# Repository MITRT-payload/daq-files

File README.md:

# daq-files
For the data acquisition

DAQ Files for Hermes III under daqr2/

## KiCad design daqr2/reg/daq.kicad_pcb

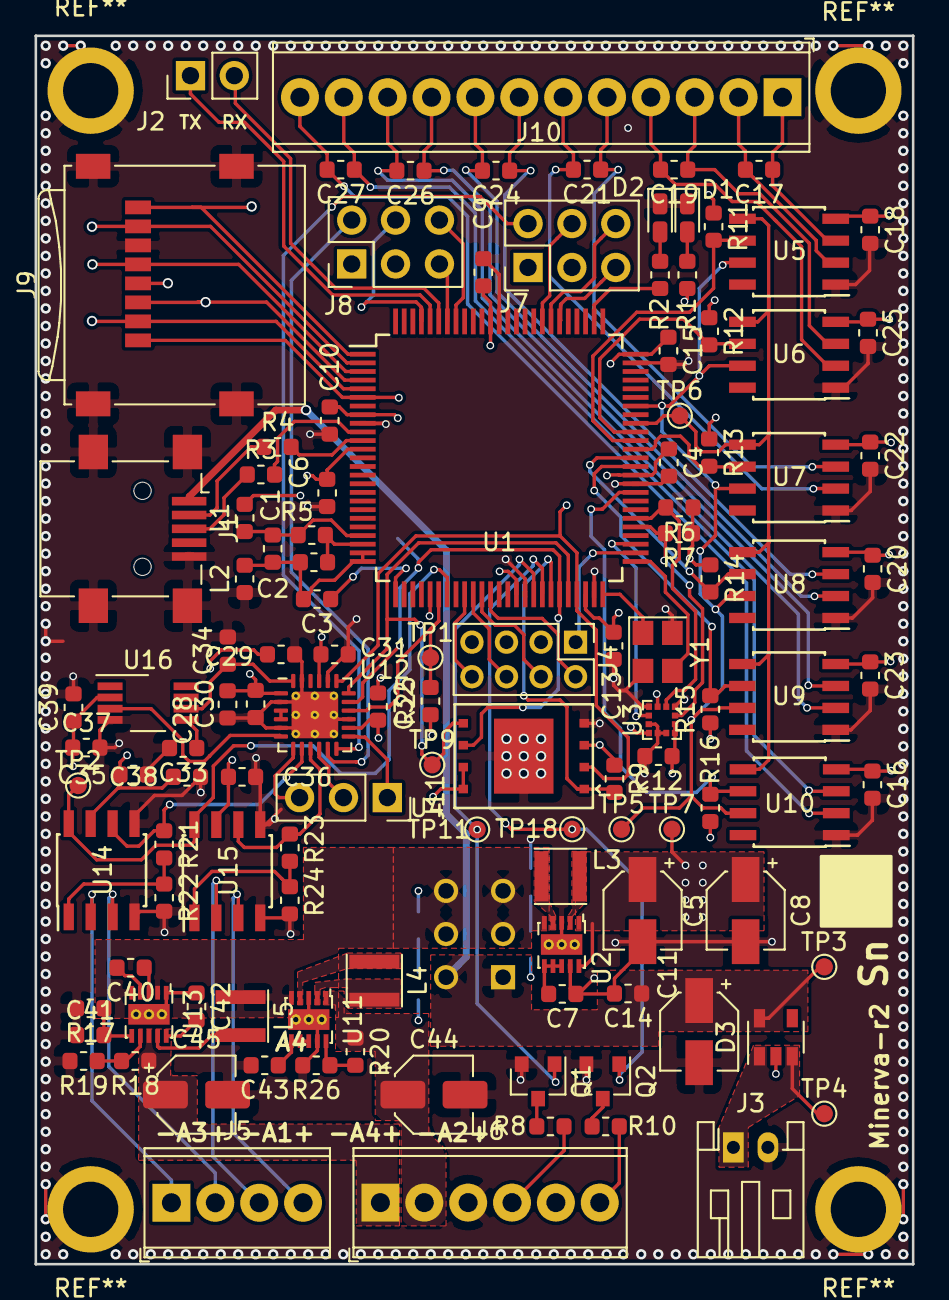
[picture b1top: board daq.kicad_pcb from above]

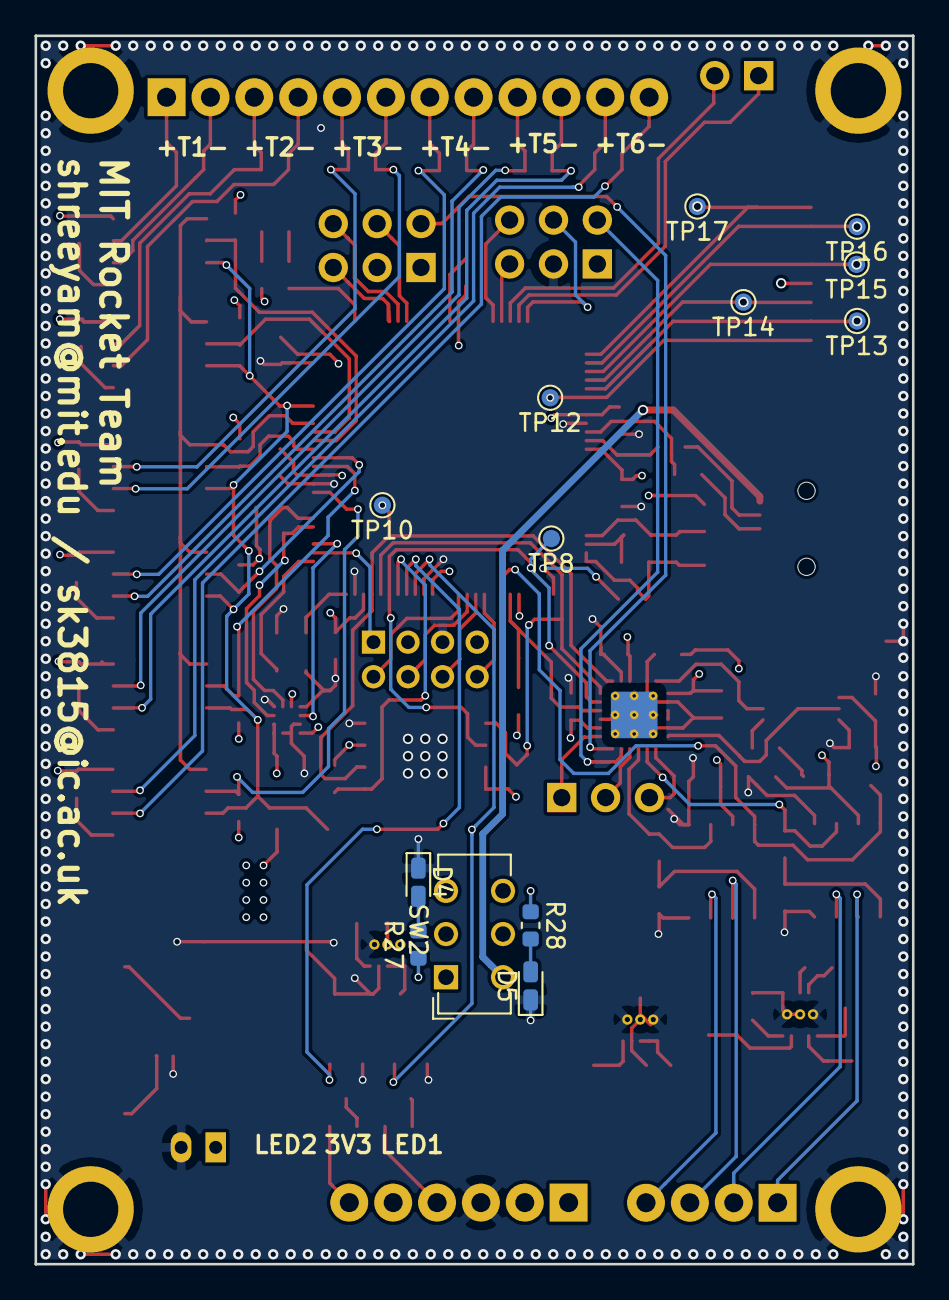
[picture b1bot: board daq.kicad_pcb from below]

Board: 4 copper layers, 50.8 x 71.1 mm, 132 parts (13 on the bottom side), 106 nets.

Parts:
C1, C29, C30, C31, C32: 2.2uF; C_0603_1608Metric
C2, C3, C4, C6, C7, C9, C10, C12, C13, C14, C15, C16, C18, C20, C22, C23, C25, C28, C35, C36, C38, C39, C43: 100nF; C_0603_1608Metric
C5, C8, C11, C44, C45: 10uF; CP_Elec_4x5.8
C17, C19, C21, C24, C26, C27: 10nF; C_0603_1608Metric
C33, C37: 1uF; C_0603_1608Metric
C34: 10uF; C_0603_1608Metric
C40, C42: 100n; C_0603_1608Metric
C41: 1u; C_0603_1608Metric
D1, D2, D4, D5: LED; LED_0603_1608Metric_Castellated
D3: MAX40200; SOT-23-5
J1: USB_B_Mini; USB_Mini-B_Lumberg_2486_01_Horizontal
J2: Conn_01x02; PinHeader_1x02_P2.54mm_Vertical
J3: Battery; JST_PH_S2B-PH-K_1x02_P2.00mm_Horizontal
J4: Programmer; PinHeader_2x04_P2.00mm_Vertical
J5: Screw_Terminal_01x04; TerminalBlock_Phoenix_MPT-0,5-4-2.54_1x04_P2.54mm_Horizontal
J6: Driven LEDs; TerminalBlock_Phoenix_MPT-0,5-6-2.54_1x06_P2.54mm_Horizontal
J7: Accelerometer 1; PinHeader_2x03_P2.54mm_Vertical
J8: Accelerometer 2; PinHeader_2x03_P2.54mm_Vertical
J9: Micro_SD_Card; microSD_HC_Wuerth_693072010801
J10: Thermocouple Input; TerminalBlock_Phoenix_MPT-0,5-12-2.54_1x12_P2.54mm_Horizont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
J11: Conn_01x02; PinSocket_1x03_P2.54mm_Vertical
L1, L2: L_Core_Ferrite; L_0603_1608Metric
L3, L4: 1.5uH; L_Taiyo-Yuden_NR-30xx
L5: 10u; L_Taiyo-Yuden_NR-30xx
Q1, Q2: Q_NMOS_GSD; SOT-23
R1, R2, R5, R27, R28: 470; R_0603_1608Metric
R3, R4, R8, R10: 33; R_0603_1608Metric
R6, R7: 4k7; R_0603_1608Metric
R9, R11, R12, R13, R14, R15, R16, R19, R25: 10k; R_0603_1608Metric
R17: 200k; R_0603_1608Metric
R18: 230k; R_0603_1608Metric
R20: 180k; R_0603_1608Metric
R21: 30k; R_0603_1608Metric
R22, R24: 1k; R_0603_1608Metric
R23: 100k; R_0603_1608Metric
R26: 20k; R_0603_1608Metric
SW2: SW_DPDT_x2; SW_CuK_JS202011CQN_DPDT_Straight
TP1: CSANLG; TestPoint_Pad_D1.0mm
TP2: CAL; TestPoint_Pad_D1.0mm
TP3: VDD; TestPoint_Pad_D1.0mm
TP4: +BATT; TestPoint_Pad_D1.0mm
TP5, TP6: TestPoint; TestPoint_Pad_D1.0mm
TP7: +3V3; TestPoint_Pad_D1.0mm
TP8: SPI0_SCLK; TestPoint_Pad_D1.0mm
TP9: SPI0_MOSI; TestPoint_Pad_D1.0mm
TP10: SPI0_MISO; TestPoint_Pad_D1.0mm
TP11: LEDE1; TestPoint_Pad_D1.0mm
TP12: SD_DAT2; TestPoint_Pad_D1.0mm
TP13: SD_DAT3; TestPoint_Pad_D1.0mm
TP14: SD_CMD; TestPoint_Pad_D1.0mm
TP15: SD_CLK; TestPoint_Pad_D1.0mm
TP16: SD_DAT0; TestPoint_Pad_D1.0mm
TP17: SD_DAT1; TestPoint_Pad_D1.0mm
TP18: LEDE2; TestPoint_Pad_D1.0mm
U1: MK64F; LQFP-100_14x14mm_P0.5mm
U2: TPS63031; VSON-10-1EP_2.5x2.5mm_Pitch0.5mm_ThermalPad
U3: KXTJ3-1057; LGA-12_2x2mm_P0.5mm
U4: W25N01GV; WSON-8 8x6mm
U5, U6, U7, U8, U9, U10: MAX31855KASA; SOIC-8_3.9x4.9mm_P1.27mm
U11: TPS63030; VSON-10-1EP_2.5x2.5mm_Pitch0.5mm_ThermalPad
U12: ADS7951; QFN-24-1EP_4x4mm_P0.5mm_EP2.7x2.7mm_ThermalVias
U13: TPS61093; VSON-10-1EP_2.5x2.5mm_Pitch0.5mm_ThermalPad
U14, U15: MCP6N11; SOIC-8_3.9x4.9mm_P1.27mm
U16: REF5025ADGK; VSSOP-8_3.0x3.0mm_P0.65mm
Y1: 16 MHz; Crystal_SMD_3225-4Pin_3.2x2.5mm

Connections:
+3V3: C4.1, C5.1, C6.1, C8.1, C9.1, C10.1, C12.1, C13.1, C15.1, C16.1, C18.1, C20.1, C22.1, C23.1, C25.1, C28.1, C29.1, C30.1, C31.1, C32.1, C35.1, C36.1, C37.1, C38.1, C39.1, J4.3, J6.5, J7.1, J8.1, J9.4, L1.2, R1.1, R6.1, R7.1, R9.1, R11.1, R12.1, R13.1, R14.1, R15.1, R16.1, R25.1, R27.1, R28.1, TP7.1, U1.8, U1.12, U1.30, U1.40, U1.48, U1.61, U1.75, U1.89, U2.1, U2.10, U3.3, U3.7, U3.10, U3.11, U4.3, U4.7, U4.8, U5.4, U6.4, U7.4, U8.4, U9.4, U10.4, U12.1, U12.14, U12.21, U14.7, U15.7, U16.2
+5V: C44.1, J6.2, R20.1, U11.1
+10V: C45.1, J6.1, R18.1, U13.8
+BATT: D3.1, D3.3, J3.1, TP4.1
/ACC_INT: U1.53, U3.5
/CAL_ANLG: TP2.1, U1.32, U14.8, U15.8
/CS_ANLG: R25.2, TP1.1, U1.31, U12.16
/CS_FLASH: R9.2, U1.44, U4.1
/CS_TC1: R11.2, U1.65, U5.6
/CS_TC2: R12.2, U1.66, U6.6
/CS_TC3: R13.2, U1.64, U7.6
/CS_TC4: R14.2, U1.63, U8.6
/CS_TC5: R15.2, U1.62, U9.6
/CS_TC6: R16.2, U1.59, U10.6
/D+: R3.2, U1.10
/D-: R4.2, U1.11
/IM3: J5.1, U14.2
/IM4: J5.3, U15.2
/IP3: J5.2, U14.3
/IP4: J5.4, U15.3
/JTAG_TCLK: J4.8, U1.34
/JTAG_TDI: J4.6, U1.35
/JTAG_TDO: J4.4, U1.36
/JTAG_TMS: J4.2, U1.37
/LED: R2.1, U1.77
/LED_E1: Q1.1, TP11.1, U1.42
/LED_E2: Q2.1, TP18.1, U1.43
/OR_1: J7.4, U1.83
/OR_2: J8.4, U1.97
/OSC_1: U1.50, Y1.1
/OSC_2: U1.51, Y1.3
/RST: J4.1, U1.52
/SCL: R7.2, U1.55, U3.12
/SDA: R6.2, U1.56, U3.2
/SD_CLK: J9.5, TP15.1, U1.3
/SD_CMD: J9.3, TP14.1, U1.4
/SD_DAT0: J9.7, TP16.1, U1.2
/SD_DAT1: J9.8, TP17.1, U1.1
/SD_DAT2: J9.1, TP12.1, U1.6
/SD_DAT3: J9.2, TP13.1, U1.5
/SPI0_MISO: TP10.1, U1.47, U4.2, U12.19
/SPI0_MOSI: TP9.1, U1.46, U4.5, U12.18
/SPI0_SCLK: TP8.1, U1.45, U4.6, U12.17
/SPI2_MISO: TP5.1, U1.69, U5.7, U6.7, U7.7, U8.7, U9.7, U10.7
/SPI2_SCLK: TP6.1, U1.67, U5.5, U6.5, U7.5, U8.5, U9.5, U10.5
/STBY_1: J7.6, U1.82
/STBY_2: J8.6, U1.93
/ST_1: J7.5, U1.81
/ST_2: J8.5, U1.94
/UART_RX: J2.2, U1.95
/UART_TX: J2.1, U1.96
/V_ACC_1: J7.2, U12.12
/V_ACC_2: J8.2, U12.11
/analog/CHIP_TEMP: U12.6, U16.3
/analog/FG3: R21.2, R22.1, U14.1
/analog/FG4: R23.2, R24.1, U15.1
/analog/OUT0: J11.1, U12.13
/analog/OUT1: J11.3, U12.7
/analog/OUT2: J11.2, U12.10
/analog/OUT3: R21.1, U12.8, U14.6
/analog/OUT4: R23.1, U12.9, U15.6
/analog/REFP: C34.1, U12.24, U16.6
/thermocouples/T1+: C17.1, J10.1, U5.3
/thermocouples/T1-: C17.2, J10.2, U5.2
/thermocouples/T2+: C19.1, J10.3, U6.3
/thermocouples/T2-: C19.2, J10.4, U6.2
/thermocouples/T3+: C21.1, J10.5, U7.3
/thermocouples/T3-: C21.2, J10.6, U7.2
/thermocouples/T4+: C24.1, J10.7, U8.3
/thermocouples/T4-: C24.2, J10.8, U8.2
/thermocouples/T5+: C26.1, J10.9, U9.3
/thermocouples/T5-: C26.2, J10.10, U9.2
/thermocouples/T6+: C27.1, J10.11, U10.3
/thermocouples/T6-: C27.2, J10.12, U10.2
GND: C4.2, C5.2, C6.2, C7.2, C8.2, C9.2, C10.2, C11.2, C12.2, C13.2, C14.2, C15.2, C16.2, C18.2, C20.2, C22.2, C23.2, C25.2, C28.2, C29.2, C30.2, C31.2, C32.2, C33.2, C34.2, C35.2, C36.2, C37.2, C38.2, C39.2, C41.1, C42.1, C43.2, C44.2, C45.2, D1.1, D2.1, D3.2, D4.1, D5.1, J1.5, J1.6, J3.2, J4.5, J4.7, J6.3, J7.3, J8.3, J9.6, J9.9, L2.1, Q1.2, Q2.2, R17.2, R19.2, R22.2, R24.2, R26.2, U1.9, U1.41, U1.49, U1.60, U1.74, U1.88, U2.3, U2.9, U2.11, U3.1, U3.4, U3.6, U3.8, U3.9, U4.4, U4.9, U5.1, U6.1, U7.1, U8.1, U9.1, U10.1, U11.3, U11.9, U11.11, U12.2, U12.5, U12.15, U12.20, U12.23, U12.25, U13.1, U13.11, U14.4, U14.5, U15.4, U15.5, U16.4, Y1.2, Y1.4
unnamed: C1.1, C2.2, C3.2, L2.2, U1.24, U1.25
unnamed: C1.2, L1.1, R5.2, U1.22
unnamed: C2.1, R5.1, U1.23
unnamed: C3.1, U1.26
unnamed: C7.1, U2.6, U2.7, U2.8
unnamed: C33.1, U16.5
unnamed: C40.1, U13.3
unnamed: C40.2, U13.4
unnamed: C41.2, R17.1, U13.6
unnamed: C42.2, U13.10
unnamed: C43.1, U11.6, U11.7, U11.8
unnamed: D1.2, R1.2
unnamed: D2.2, R2.2
unnamed: D4.2, R27.2
unnamed: D5.2, R28.2
unnamed: J1.2, R4.1
unnamed: J1.3, R3.1
unnamed: J6.4, R8.1
unnamed: J6.6, R10.1
unnamed: L3.1, U2.4
unnamed: L3.2, U2.2
unnamed: L4.1, U11.4
unnamed: L4.2, U11.2
unnamed: L5.1, SW2.2, SW2.3, SW2.5, SW2.6, U2.5, U11.5, U13.2, U13.5
unnamed: L5.2, U13.9
unnamed: Q1.3, R8.2
unnamed: Q2.3, R10.2
unnamed: R18.2, R19.1, U13.7
unnamed: R20.2, R26.1, U11.10
unnamed: U12.3, U12.4
VDD: C11.1, C14.1, D3.5, J1.1, SW2.1, SW2.4, TP3.1

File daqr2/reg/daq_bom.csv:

Ref,Qnty,Value,Cmp name,Footprint,Description,Digikey Part Number,URL,Unit Cost,Total Cost
"C1, C29, C30, C31, C32, ",5,2.2uF,C,Capacitor_SMD:C_0603_1608Metric,Unpolarized capacitor,1276-1085-1-ND,https://www.digikey.com/product-detail/en/samsung-electro-me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,0.12,0.60
"C5, C8, C11, ",3,10uF,C,Capacitor_SMD:CP_Elec_4x5.8,Unpolarized capacitor,PCE3878CT-ND,https://www.digikey.com/product-detail/en/panasonic-electron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,0.30,0.90
"C7, C2, C3, C4, C6, C9, C10, C13, C15, C14, C12, C22, C23, C25, C16, C18, C20, C35, C36, C38, C40, C41, C28, C39, ",24,100nF,C,Capacitor_SMD:C_0603_1608Metric,Unpolarized capacitor,1276-1000-1-ND,https://www.digikey.com/product-detail/en/samsung-electro-me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,0.04,0.84
"C17, C19, C21, C24, C26, C27, ",12,10nF,C,Capacitor_SMD:C_0603_1608Metric,Unpolarized capacitor,1276-1921-1-ND,https://www.digikey.com/product-detail/en/samsung-electro-me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,0.03,0.40
"C33, C37, ",10,1uF,C,Capacitor_SMD:C_0603_1608Metric,Unpolarized capacitor,1276-1036-1-ND,https://www.digikey.com/product-detail/en/samsung-electro-me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,0.03,0.31
"C34, ",1,10uF,C,Capacitor_SMD:C_0603_1608Metric,Unpolarized capacitor,587-5869-1-ND,https://www.digikey.com/product-detail/en/taiyo-yuden/JMK107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,0.15,0.15
"D1, D2, ",2,LED,LED,LED_SMD:LED_0603_1608Metric_Castellated,LED generic,732-4971-1-ND,https://www.digikey.com/product-detail/en/wurth-electronics-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,0.15,0.30
"D3, ",1,MAX40200,MAX40200,Package_TO_SOT_SMD:SOT-23-5,,MAX40200AUK+TCT-ND,https://www.digikey.com/product-detail/en/maxim-integrated/M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,0.93,0.93
"J1, ",1,USB_B_Mini,USB_B_Micro,Connector_USB:USB_Mini-B_Lumberg_2486_01_Horizontal,USB Micro Type B connector,151-1206-1-ND,https://www.digikey.com/product-detail/en/edac-inc/690-005-2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,0.60,0.60
"J3, ",1,Battery,Conn_01x02,Connector_JST:JST_PH_S2B-PH-K_1x02_P2.00mm_Horizontal,"Generic connector, single row, 01x02, script generated (kicad-library-utils/schlib/autogen/connector/)",WM14854-ND,https://www.digikey.com/products/en?keywords=894010210,0.14,0.14
"J4, ",1,Programmer,Conn_02x04_Odd_Even,Connector_PinHeader_2.00mm:PinHeader_2x04_P2.00mm_Vertical,"Generic connector, double row, 02x04, odd/even pin numbering scheme (row 1 odd numbers, row 2 even numbers), script generated (kicad-library-utils/schlib/autogen/connector/)",A108094-ND,https://www.digikey.com/products/en?keywords=2-1734506-7,0.59,0.59
"J5, ",1,Pressure Tap/Load Cell,Screw_Terminal_01x08,"TerminalBlock_Phoenix:TerminalBlock_Phoenix_MPT-0,5-8-2.54_1x08_P2.54mm_Horizontal","Generic screw terminal, single row, 01x08, script generated (kicad-library-utils/schlib/autogen/connector/)",ED10566-ND,https://www.digikey.com/product-detail/en/on-shore-technolog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,2.36,2.36
"J6, ",1,Driven LEDs,Screw_Terminal_01x03,"custom:TerminalBlock_Phoenix_MPT-0,5-3-2.54_1x03_P2.54mm_Horizontal","Generic screw terminal, single row, 01x03, script generated (kicad-library-utils/schlib/autogen/connector/)",ED10562-ND,https://www.digikey.com/product-detail/en/on-shore-technolog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,1.03,1.03
"J7, J8",2,Accelerometer,Conn_02x03_Odd_Even,Connector_PinHeader_2.54mm:PinHeader_2x03_P2.54mm_Vertical,"Generic connector, double row, 02x03, odd/even pin numbering scheme (row 1 odd numbers, row 2 even numbers), script generated (kicad-library-utils/schlib/autogen/connector/)",S7071-ND,https://www.digikey.com/product-detail/en/sullins-connector-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,0.61,1.22
"J9, ",1,Micro_SD_Card,Micro_SD_Card,Connector_Card:microSD_HC_Wuerth_693072010801,Micro SD Card Socket,732-3820-1-ND,https://www.digikey.com/product-detail/en/wurth-electronics-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,3.42,3.42
"J10, ",1,Thermocouple Input,Screw_Terminal_01x12,"TerminalBlock_Phoenix:TerminalBlock_Phoenix_MPT-0,5-12-2.54_1x12_P2.54mm_Horizontal","Generic screw terminal, single row, 01x12, script generated (kicad-library-utils/schlib/autogen/connector/)",ED10568-ND,https://www.digikey.com/product-detail/en/on-shore-technolog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,3.16,3.16
"L1, L2, ",2,L_Core_Ferrite,L_Core_Ferrite,Inductor_SMD:L_0603_1608Metric,Inductor with Ferrite Core,1276-6351-1-ND,https://www.digikey.com/product-detail/en/samsung-electro-me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,0.10,0.20
"L3, ",1,1.5uH,L,Inductor_SMD:L_Taiyo-Yuden_NR-30xx,Inductor,587-2617-1-ND,https://www.digikey.com/product-detail/en/taiyo-yuden/NR3015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,0.41,0.41
"Q1, Q2, ",2,Q_NMOS_GSD,Q_NMOS_GSD,Package_TO_SOT_SMD:SOT-23,Transistor N-MOSFETwith substrate diode (general),NTR5103NT1GOSCT-ND,https://www.digikey.com/product-detail/en/on-semiconductor/N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,0.18,0.36
"R5, R1, R2, ",3,470,R,Resistor_SMD:R_0603_1608Metric,Resistor,311-470GRCT-ND,https://www.digikey.com/product-detail/en/yageo/RC0603JR-074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,0.10,0.30
"R6, R7, ",10,4k7,R,Resistor_SMD:R_0603_1608Metric,Resistor,311-4.7KGRCT-ND,https://www.digikey.com/product-detail/en/yageo/RC0603JR-074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,0.02,0.20
"R8, R10, R4, R3, ",4,33,R,Resistor_SMD:R_0603_1608Metric,Resistor,311-33.0HRCT-ND,https://www.digikey.com/product-detail/en/yageo/RC0603FR-073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,0.10,0.40
"R9, R11, R12, R13, R14, R15, R16, R25, ",20,10k,R,Resistor_SMD:R_0603_1608Metric,Resistor,RMCF0603JT10K0CT-ND,https://www.digikey.com/product-detail/en/stackpole-electron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,0.02,0.32
"R17, R19, R21, ",10,30k,R,Resistor_SMD:R_0603_1608Metric,Resistor,RMCF0603JT30K0CT-ND,https://www.digikey.com/product-detail/en/stackpole-electron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,0.02,0.16
"R18, R20, R22, R24, ",10,1k,R,Resistor_SMD:R_0603_1608Metric,Resistor,RMCF0603FT1K00CT-ND,https://www.digikey.com/product-detail/en/stackpole-electron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,0.02,0.18
"R23, ",10,100k,R,Resistor_SMD:R_0603_1608Metric,Resistor,CR0603-JW-104ELFCT-ND,https://www.digikey.com/product-detail/en/bourns-inc/CR0603-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,0.02,0.15
"SW1, ",1,SW_SPST,SW_SPST,Button_Switch_THT:SW_DIP_SPSTx01_Slide_9.78x4.72mm_W7.62mm_P2.54mm,Single Pole Single Throw (SPST) switch,Z5195-ND,https://www.digikey.com/product-detail/en/omron-electronics-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,0.90,0.90
"U1, ",1,MK64F,MK64F,Package_QFP:LQFP-100_14x14mm_P0.5mm,,MK64FX512VLL12-ND,https://www.digikey.com/product-detail/en/nxp-usa-inc/MK64FX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,12.56,12.56
"U2, ",1,TPS63031,TPS63031,custom:VSON-10-1EP_2.5x2.5mm_Pitch0.5mm_ThermalPad,,296-39461-1-ND,https://www.digikey.com/product-detail/en/texas-instruments/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,1.93,1.93
"U3, ",1,KXTJ3-1057,KXTJ3-1057,Package_LGA:LGA-12_2x2mm_P0.5mm,,KXTJ3-1057CT-ND,https://www.digikey.com/product-detail/en/kionix-inc/KXTJ3-1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,1.69,1.69
"U4, ",1,W25N01GV,W25N01GV,custom:WSON-8 8x6mm,,W25N01GVZEIGCT-ND,https://www.digikey.com/product-detail/en/winbond-electronic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,3.27,3.27
"U5, U6, U7, U8, U9, U10, ",6,MAX31855KASA,MAX31855KASA,Package_SO:SOIC-8_3.9x4.9mm_P1.27mm,"Cold Junction K-type Termocouple Interface, SPI, SO8",MAX31855KASA+TCT-ND,https://www.digikey.com/product-detail/en/maxim-integrated/M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,6.52,39.12
"U11, U13, U14, U15, ",4,MCP6N11,MCP6N11,Package_SO:SOIC-8_3.9x4.9mm_P1.27mm,,MCP6N11-010E/SN-ND,https://www.digikey.com/products/en?keywords=MCP6N11-010,1.39,5.56
"U12, ",1,ADS7951,ADS7951,Package_DFN_QFN:QFN-24-1EP_4x4mm_P0.5mm_EP2.7x2.7mm_ThermalVias,,296-25840-1-ND,https://www.digikey.com/product-detail/en/texas-instruments/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,7.44,7.44
"U16, ",1,REF5025ADGK,REF5025ADGK,Package_SO:VSSOP-8_3.0x3.0mm_P0.65mm,"2.5V 0.1% 10mA Low Noise Precision Voltage Reference, MSOP-8",296-41382-1-ND,https://www.digikey.com/product-detail/en/texas-instruments/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,3.00,3.00
"Y1, ",1,16 MHz,Crystal_GND24,Crystal:Crystal_SMD_3225-4Pin_3.2x2.5mm,"Four pin crystal (GND on pins 2 and 4), e.g. in SMD package",644-1099-1-ND,https://www.digikey.com/product-detail/en/ndk-america-inc/NX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,0.92,0.92
,,,,,,,,,96.016

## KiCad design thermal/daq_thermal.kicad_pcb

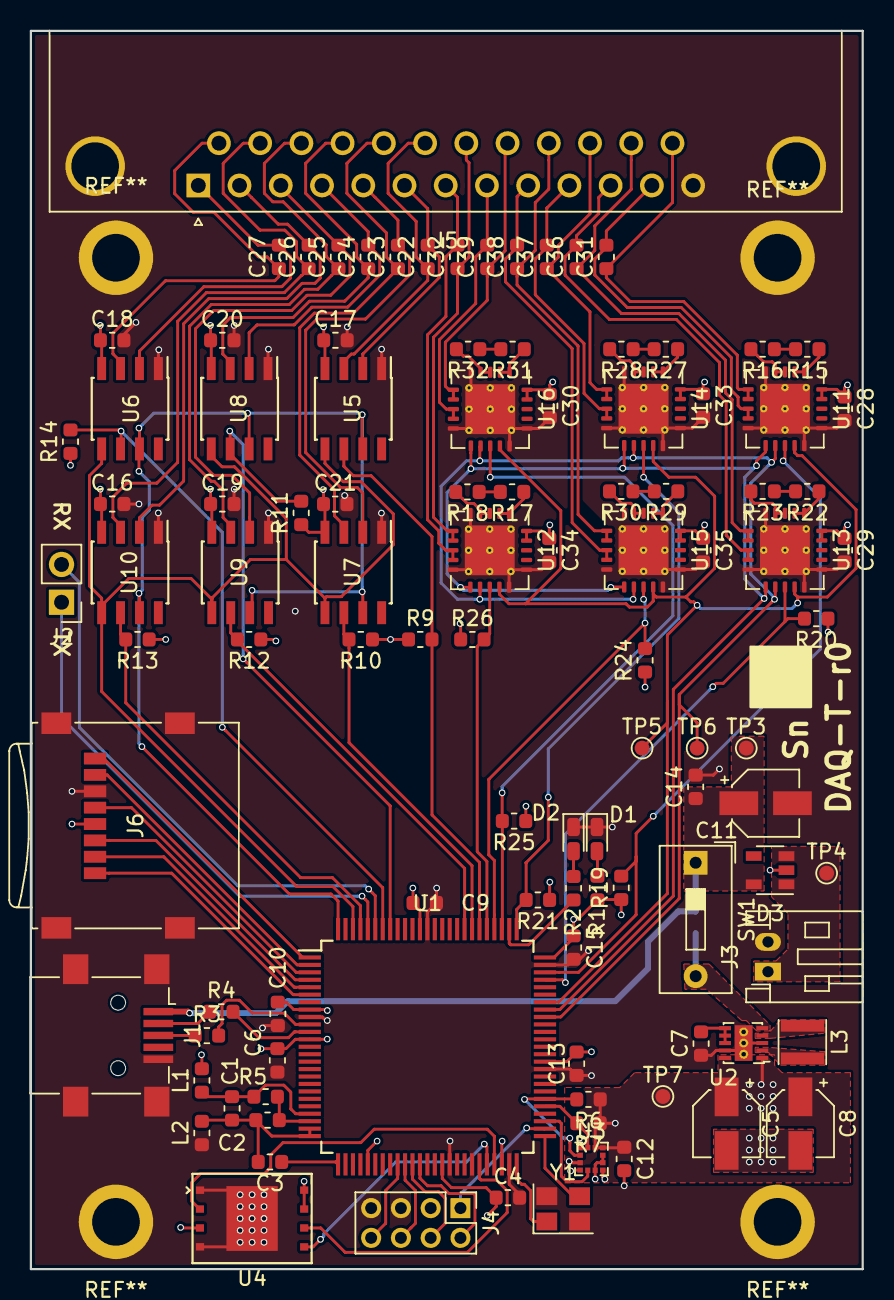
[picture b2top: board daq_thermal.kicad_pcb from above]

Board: 4 copper layers, 55.9 x 83.2 mm, 106 parts (1 on the bottom side), 99 nets.

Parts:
C1: 2.2uF; C_0603_1608Metric
C2, C3, C4, C6, C7, C9, C10, C12, C13, C14, C15, C16, C17, C18, C19, C20, C21: 100nF; C_0603_1608Metric
C5, C8, C11: 10uF; CP_Elec_4x5.8
C22, C23, C24, C25, C26, C27: 10nf; C_0603_1608Metric
C28, C29, C30, C33, C34, C35: 220nF; C_0603_1608Metric
C31, C32, C36, C37, C38, C39: 10nF; C_0603_1608Metric
D1, D2: LED; LED_0603_1608Metric_Castellated
D3: MAX40200; SOT-23-5
J1: USB_B_Mini; USB_Mini-B_Lumberg_2486_01_Horizontal
J2: Conn_01x02; PinHeader_1x02_P2.54mm_Vertical
J3: Battery; JST_PH_S2B-PH-K_1x02_P2.00mm_Horizontal
J4: Programmer; PinHeader_2x04_P2.00mm_Vertical
J5: Dsub25; DSUB-25_Male_Horizontal_P2.77x2.84mm_EdgePinOffset4.94mm_Ho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
J6: Micro_SD_Card; microSD_HC_Wuerth_693072010801
JP1: SolderJumper_2_Open; SolderJumper-2_P1.3mm_Open_TrianglePad1.0x1.5mm
L1, L2: L_Core_Ferrite; L_0603_1608Metric
L3: 1.5uH; L_Taiyo-Yuden_NR-30xx
R1, R2, R5: 470; R_0603_1608Metric
R3, R4: 33; R_0603_1608Metric
R6, R7: 4k7; R_0603_1608Metric
R9, R10, R11, R12, R13, R14, R19, R20, R21, R24, R25, R26: 10k; R_0603_1608Metric
R15, R16, R17, R18, R22, R23, R27, R28, R29, R30, R31, R32: 2k; R_0603_1608Metric
SW1: SW_SPST; SW_DIP_SPSTx01_Slide_9.78x4.72mm_W7.62mm_P2.54mm
TP3: VDD; TestPoint_Pad_D1.0mm
TP4: +BATT; TestPoint_Pad_D1.0mm
TP5, TP6: TestPoint; TestPoint_Pad_D1.0mm
TP7: +3V3; TestPoint_Pad_D1.0mm
U1: MK64F; LQFP-100_14x14mm_P0.5mm
U2: TPS63031; VSON-10-1EP_2.5x2.5mm_Pitch0.5mm_ThermalPad
U3: KXTJ3-1057; LGA-12_2x2mm_P0.5mm
U4: W25N01GV; WSON-8 8x6mm
U5, U6, U7, U8, U9, U10: MAX31855KASA; SOIC-8_3.9x4.9mm_P1.27mm
U11, U12, U13, U14, U15, U16: MAX31865; QFN-20-1EP_5x5mm_P0.65mm_EP3.35x3.35mm_ThermalVias
Y1: 16 MHz; Crystal_SMD_3225-4Pin_3.2x2.5mm

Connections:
+3V3: C4.1, C5.1, C6.1, C8.1, C9.1, C10.1, C12.1, C13.1, C15.1, C16.1, C17.1, C18.1, C19.1, C20.1, C21.1, C28.1, C29.1, C30.1, C33.1, C34.1, C35.1, J4.3, J6.4, L1.2, R1.1, R6.1, R7.1, R9.1, R10.1, R11.1, R12.1, R13.1, R14.1, R19.1, R20.1, R21.1, R24.1, R25.1, R26.1, TP7.1, U1.8, U1.12, U1.30, U1.40, U1.48, U1.61, U1.75, U1.89, U2.1, U2.10, U3.3, U3.7, U3.10, U3.11, U4.3, U4.7, U4.8, U5.4, U6.4, U7.4, U8.4, U9.4, U10.4, U11.19, U11.20, U12.19, U12.20, U13.19, U13.20, U14.19, U14.20, U15.19, U15.20, U16.19, U16.20
+BATT: D3.1, D3.3, J3.1, TP4.1
/ACC_INT: U1.53, U3.5
/CS_RTD1: R19.2, U1.73, U11.13
/CS_RTD2: R20.2, U1.72, U13.13
/CS_RTD3: R21.2, U1.76, U14.13
/CS_RTD4: R24.2, U1.79, U15.13
/CS_RTD5: R25.2, U1.78, U16.13
/CS_RTD6: R26.2, U1.80, U12.13
/CS_TC1: R9.2, U1.81, U5.6
/CS_TC2: R10.2, U1.82, U7.6
/CS_TC3: R11.2, U1.93, U8.6
/CS_TC4: R12.2, U1.83, U9.6
/CS_TC5: R13.2, U1.97, U10.6
/CS_TC6: R14.2, U1.94, U6.6
/D+: R3.2, U1.10
/D-: R4.2, U1.11
/LED: R2.1, U1.77
/OSC_1: U1.50, Y1.1
/OSC_2: U1.51, Y1.3
/PTA0: J4.8, U1.34
/PTA1: J4.6, U1.35
/PTA2: J4.4, U1.36
/PTA3: J4.2, U1.37
/RST: J4.1, U1.52
/RTD1+: C31.1, J5.25, U11.6, U11.7
/RTD1-: C31.2, J5.12, U11.8, U11.9
/RTD2+: C36.1, J5.24, U13.6, U13.7
/RTD2-: C36.2, J5.11, U13.8, U13.9
/RTD3+: C37.1, J5.23, U14.6, U14.7
/RTD3-: C37.2, J5.10, U14.8, U14.9
/RTD4+: C38.1, J5.22, U15.6, U15.7
/RTD4-: C38.2, J5.9, U15.8, U15.9
/RTD5+: C39.1, J5.21, U16.6, U16.7
/RTD5-: C39.2, J5.8, U16.8, U16.9
/RTD6+: C32.1, J5.20, U12.6, U12.7
/RTD6-: C32.2, J5.7, U12.8, U12.9
/SCL: R7.2, U1.55, U3.12
/SDA: R6.2, U1.56, U3.2
/SD_CLK: J6.5, U1.3
/SD_CMD: J6.3, U1.4
/SD_DAT0: J6.7, U1.2
/SD_DAT1: J6.8, U1.1
/SD_DAT2: J6.1, U1.6
/SD_DAT3: J6.2, U1.5
/SPI0_MISO: U1.47, U4.2
/SPI0_MOSI: U1.46, U4.5
/SPI0_SCLK: U1.45, U4.6
/SPI1_MISO: U1.100, U5.7, U6.7, U7.7, U8.7, U9.7, U10.7
/SPI1_SCLK: U1.98, U5.5, U6.5, U7.5, U8.5, U9.5, U10.5
/SPI2_MISO: TP5.1, U1.69, U11.14, U12.14, U13.14, U14.14, U15.14, U16.14
/SPI2_MOSI: U1.68, U11.11, U12.11, U13.11, U14.11, U15.11, U16.11
/SPI2_SCLK: TP6.1, U1.67, U11.12, U12.12, U13.12, U14.12, U15.12, U16.12
/TC1+: C22.1, J5.19, U5.3
/TC1-: C22.2, J5.6, U5.2
/TC2+: C23.1, J5.18, U7.3
/TC2-: C23.2, J5.5, U7.2
/TC3+: C24.1, J5.17, U8.3
/TC3-: C24.2, J5.4, U8.2
/TC4+: C25.1, J5.16, U9.3
/TC4-: C25.2, J5.3, U9.2
/TC5+: C26.1, J5.15, U10.3
/TC5-: C26.2, J5.2, U10.2
/TC6+: C27.1, J5.14, U6.3
/TC6-: C27.2, J5.1, U6.2
/UART_RX: J2.2, U1.95
/UART_TX: J2.1, U1.96
GND: C4.2, C5.2, C6.2, C7.2, C8.2, C9.2, C10.2, C11.2, C12.2, C13.2, C14.2, C15.2, C16.2, C17.2, C18.2, C19.2, C20.2, C21.2, C28.2, C29.2, C30.2, C33.2, C34.2, C35.2, D1.1, D2.1, D3.2, J1.5, J1.6, J3.2, J4.5, J4.7, J5.0, J5.13, J6.6, J6.9, L2.1, U1.9, U1.41, U1.44, U1.49, U1.60, U1.74, U1.88, U2.3, U2.9, U2.11, U3.1, U3.4, U3.6, U3.8, U3.9, U4.1, U4.4, U4.9, U5.1, U6.1, U7.1, U8.1, U9.1, U10.1, U11.5, U11.10, U11.15, U11.16, U11.21, U12.5, U12.10, U12.15, U12.16, U12.21, U13.5, U13.10, U13.15, U13.16, U13.21, U14.5, U14.10, U14.15, U14.16, U14.21, U15.5, U15.10, U15.15, U15.16, U15.21, U16.5, U16.10, U16.15, U16.16, U16.21, Y1.2, Y1.4
unnamed: C1.1, C2.2, C3.2, L2.2, U1.24, U1.25
unnamed: C1.2, L1.1, R5.2, U1.22
unnamed: C2.1, R5.1, U1.23
unnamed: C3.1, U1.26
unnamed: C7.1, U2.6, U2.7, U2.8
unnamed: D1.2, R1.2
unnamed: D2.2, R2.2
unnamed: J1.2, R4.1
unnamed: J1.3, R3.1
unnamed: JP1.2, SW1.2, U2.5
unnamed: L3.1, U2.4
unnamed: L3.2, U2.2
unnamed: R15.1, U11.1, U11.2
unnamed: R15.2, R16.1
unnamed: R16.2, U11.3, U11.4
unnamed: R17.1, U12.1, U12.2
unnamed: R17.2, R18.1
unnamed: R18.2, U12.3, U12.4
unnamed: R22.1, U13.1, U13.2
unnamed: R22.2, R23.1
unnamed: R23.2, U13.3, U13.4
unnamed: R27.1, U14.1, U14.2
unnamed: R27.2, R28.1
unnamed: R28.2, U14.3, U14.4
unnamed: R29.1, U15.1, U15.2
unnamed: R29.2, R30.1
unnamed: R30.2, U15.3, U15.4
unnamed: R31.1, U16.1, U16.2
unnamed: R31.2, R32.1
unnamed: R32.2, U16.3, U16.4
VDD: C11.1, C14.1, D3.5, J1.1, JP1.1, SW1.1, TP3.1

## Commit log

2019-09-02 thermal and nc daq
    files from kicad
2019-10-27 feat: comment update
2019-11-09 Add r2 daq LE files
    from shreeyam
2020-01-14 Create README.md
    add info
